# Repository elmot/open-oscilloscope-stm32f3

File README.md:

## Open-Source Oscilloscope based on NUCLEO-F303RE

Some ideas got from Tomasz Ostrowski's [Miniscope](http://tomeko.net/miniscope_v4/index.php?lang=en).
Tomasz has a bunch of ready-to-use-devices, and I have the only preliminary schematics and raw prototype.

The main idea is to build PC-oscilloscope. Hardware is ST Microelectronics development board
[NUCLEO-F303RE](http://www.st.com/en/evaluation-tools/nucleo-f303re.html) plus small additional board with simple protection circuits and basic voltage dividers.

A special Java application or web browser is supposed to be a PC part of the system.

## DISCLAIMER

**! WARNING !**

Read [SAFETY DISCLAIMER](DISCLAIMER.md) before using any of materials listed here.  

### License:
[MIT](license.txt)

### Hardware variants
* Naked Nucleo
  * _No overvoltage protection_
  * Input voltage: 0..3V uni-polar
* Shield board + Nucleo
  * Overvoltage protection
  * Input voltage: 0..30V uni-polar
  * Max. input impedance ~200kOhm

### Usage HOWTO
TBD

### Build HOWTO

#### Required tools
* cmake 3.9.x
* arm-none-eabi-gcc 5.4 + binutils

#### Build firmware
* `mkdir target`
* `cd target`
* `cmake -DCMAKE_TOOLCHAIN_FILE=STM32F303RETx_FLASH.cmake ..`
* `make`

#### Flash firmware
* Connect NUCLEO board
* Copy generated file (_cmake-build-debug/f3_nucleo_oscilloscope.bin_) to NUCLEO virtual drive
* Unmount NUCLEO virtual drive
 
### Roadmap
See [ROADMAP.md](ROADMAP.md)

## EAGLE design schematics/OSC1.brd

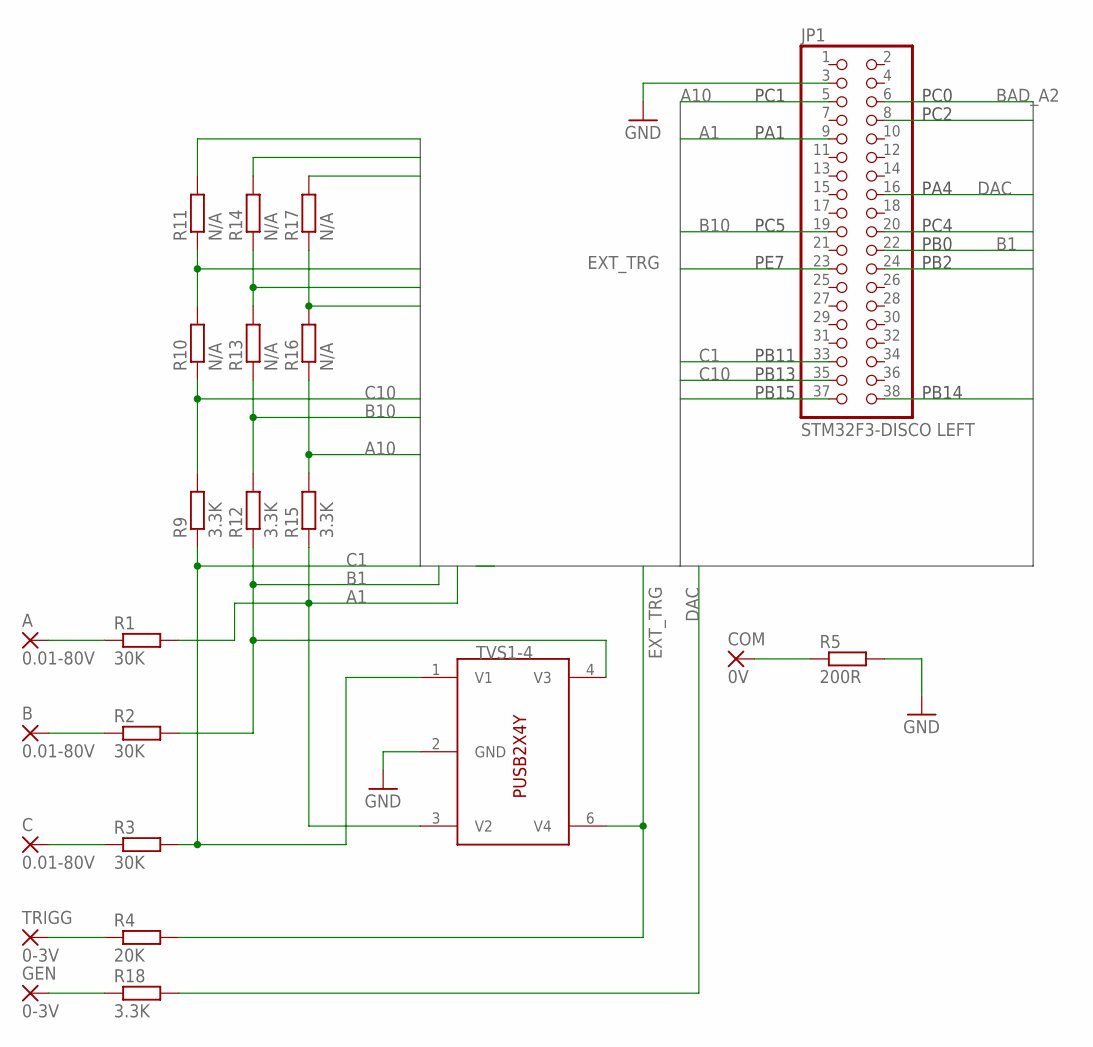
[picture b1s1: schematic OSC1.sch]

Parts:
A: 0.01-80V; 2,54/0,8
B: 0.01-80V; 2,54/0,8
C: 0.01-80V; 2,54/0,8
COM: 0V; 2,54/0,8
GEN: 0-3V; 2,54/0,8
JP1: STM32F3-DISCO LEFT; 2X19
R1, R2, R3: 30K; R1206
R4: 20K; R1206
R5: 200R; R1206
R9, R12, R15, R18: 3.3K; R1206
R10, R11, R13, R14, R16, R17: N/A; R1206
TRIGG: 0-3V; 2,54/0,8
TVS1-4: PUSB2X4Y; SOT363_PHILIPS

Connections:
A1: JP1.9, R1.2, R15.1, TVS1-4.3 (V2)
A10: JP1.5, R15.2, R16.1
B1: JP1.22, R2.2, R12.1, TVS1-4.4 (V3)
B10: JP1.19, R12.2, R13.1
BAD_A2: JP1.6, R17.2
BAD_A10: JP1.8, R16.2, R17.1
BAD_B2: JP1.24, R14.2
BAD_B10: JP1.20, R13.2, R14.1
BAD_C2: JP1.38, R11.2
BAD_C10: JP1.37, R10.2, R11.1
C1: JP1.33, R3.2, R9.1, TVS1-4.1 (V1)
C10: JP1.35, R9.2, R10.1
DAC: JP1.16, R18.2
EXT_TRG: JP1.23, R4.2, TVS1-4.6 (V4)
GND: JP1.3, R5.2, TVS1-4.2 (GND)
unnamed: COM.1, R5.1
unnamed: A.1, R1.1
unnamed: R4.1, TRIGG.1
unnamed: C.1, R3.1
unnamed: B.1, R2.1
unnamed: GEN.1, R18.1

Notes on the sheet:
PA1
PB11
PB0
PA4
PC1
PC0
PC2
PB2
PC4
PC5
PB13
PB14
PB15
PE7

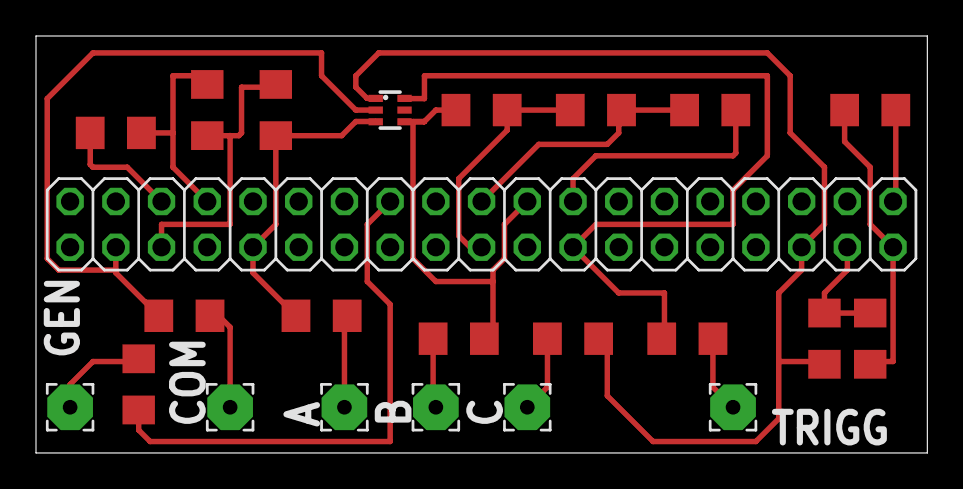
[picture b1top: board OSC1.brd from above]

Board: 2 copper layers, 49.5 x 23.2 mm, 23 parts (0 on the bottom side), 21 nets.

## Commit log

2015-11-21 USB exchange
2016-01-18 Chrome client 1st prototype, USB data exchange works
2016-01-18 removed useless stuff
2016-01-18 PCB picture added
2016-01-19 Gain control; Fixed timing; triangle generation; UI improvements
2016-01-19 Published to Chrome Store
2016-01-21 New icon
2016-01-21 Unnecessary files removed
2016-01-21 Better parameters handling.
2016-01-21 Timing, Range instead of gain, better design
2016-01-21 Ignore. iex
2016-01-21 Pin names corrected
2016-01-21 Latest binary
2016-01-21 Latest screenshots
2016-01-21 Version updated
2016-01-22 Readme updated
2016-01-22 A2 &A 10 fixed
2016-01-23 3 channels, different timing up to 5MHz
2016-01-23 No Jannson
2016-01-23 Pins fixes
2016-01-23 Three channels
2016-01-23 Refactoring+three channels support
2016-01-23 Range fixed
2016-01-23 3 channels; CubeMX bug workaround
2016-01-23 3 channels
2016-01-23 3 Channels work for the very first time.
2016-01-23 Shitty code fix
2016-01-23 UI improvements, refactoring
2016-01-23 Trigger Channel A support, refactoring
2016-01-24 Fast mode dropped from roadmap + small changes
2016-01-24 UI improvements
2016-01-24 Refactoring
2016-01-24 3 channel triggers
2016-01-24 Drop non-key frame if key frame is received
2016-01-24 Triggers better support, refactoring
2016-01-24 No DMA mem-to-mem
2016-01-24 Curve shapes improved
2016-01-24 Market update v.0.0.3
2016-01-25 Non-key frame buffering, better trigger stability
2016-01-25 select_tests
2016-01-25 Play around options
2017-02-05 Restart almost from scratch, new CubeMX, USB CDC instead of USB Vendor-Specific
2017-02-05 DMA_IRQ_SETTINGS
2017-02-05 Semihosting lib
2017-02-05 DMA interrupts and basic data copy
2017-02-06 USB Support started.
2017-02-07 Send data step 1
2017-02-08 JavaFX client
2017-03-05 Single-channel, no triggers
2017-03-07 JavaFX + RXTX library
2017-03-07 next step towards to triggers
2017-03-09 Unfinished web gateway
2017-03-09 Semihosting detection
2017-03-10 Http version phase I
2017-03-10 Http version phase II
2017-03-11 Web part ms 1 works, ready to implement HW commands
2017-03-13 Step 2 towards to triggers
2017-03-13 ADC high rate problem detected but not fixed
2017-03-14 ADC high rate fixed
2017-03-14 Frame queue reset when command is sent to the device
2017-03-14 Cube rerun
2017-03-14 JS optimization
2017-03-14 Some improvements
2017-03-15 Fix typo
2017-03-15 Trigger works 1/2
2017-03-15 Next step towards to trigger
2017-03-16 Switch ACM protocol version to 0
2017-03-16 UART recv binary error detection
2017-03-16 Triggers work. Pre-trigger has glitches
2017-03-16 Some fixes
2017-03-16 Unified command parse
2017-03-17 Gen step 1
2017-03-17 Java FX is not supported
2017-03-17 No AT protocol in USB CDC descriptor
2017-03-17 Generator works
2017-03-17 STM Virtual Port driver for Windows is added
2017-03-17 icons+html improvements
2017-03-17 Front update (#2)
    Front update, html improvements
2017-03-17 Restore app icon
2017-03-17 Sine wave; Less generator overhead
2017-03-17 Skip garbage from UART?
2017-03-17 Resolve race conditions?
2017-03-17 Restore dividers for chanel B
2017-03-17 Error message more visible
2017-03-17 Store and init confids, part 1
2017-03-17 Comm. protocol v1.1
2017-03-18 icon fix
2017-03-18 Comm. protocol v2.0
2017-03-19 Don't ignore .exe
2017-03-19 No gzip, better error handling
2017-03-19 NPE protection
2017-03-19 Buggy frame bursting
2017-03-19 Frame bursting fix
2017-03-19 Refactiring and fixes
2017-03-19 Some fixes; diagnostics; config sync; reasonable defaults
2017-03-19 Get rid of CommThread
2017-03-19 JavaFX version works again
2017-03-19 Com port choice in JavaFX app
2017-03-20 JavaFX optimised and fixed
2017-03-20 Various timing fixes
2017-03-21 CMake issue fixed
2017-03-21 .hex and .bin files generation
2017-03-21 Universal CLI launcher
2017-03-21 No extra Thread.yield
2017-03-21 Better screen update timing
2017-03-21 Build .dfu, fix 'make clean'
2017-03-21 Documentation
2017-03-21 Release script
2017-03-21 Fix links
2017-03-21 Fix Disclaimer
2017-03-21 Temporary disable channels B and C
2017-03-22 More stable communications, setting port
2017-03-22 Optimize FPS counter
2017-03-22 Numerous fixes and improvements
2017-03-22 Small improvements
2017-03-23 Release assembly process with mvn
2017-03-23 Parameters setting improvements
2017-03-23 Ship both web and javafx versions
2017-03-23 Voltage/time outpur
2017-03-24 PCB files merged from another branch
2017-03-24 - Electrical parameters change - schematics + readme
2017-03-24 - Electrical parameters change - FirmWare
2017-03-24 Firmware initial settings fixed
2017-03-24 - Electrical parameters change - Client
2017-03-24 Change buffering default
2017-04-04 Timing and voltage units displayed
2017-04-04 Fix trigger picking off
2017-04-09 Measurements + some refactoring
2017-04-16 SVD->C generator first draft
2017-04-16 OpenOCD/extrenal GDB support
2017-04-16 SVD generator support 1st try
2017-04-16 Small fix
2017-04-17 Upgrade to next cube
2017-04-17 New peripheral generator
2017-04-17 No packed attribute
2017-04-17 Alternative registers to unions.
2017-05-02 Roughly fix line feeds
2017-05-02 Make like utility
2017-06-10 Basic triangle generator
2017-06-10 TFMs
2017-06-11 Electron client
2017-06-11 Run configurations
2017-06-11 Simple data transfer
2017-06-14 Basic electron client
2017-06-26 NW.js client instead of electron
2017-06-26 Add hardware definitions
2017-06-26 nw client runner
2017-06-27 Basic triggers, no copy frame yet
2017-07-03 Send keyframes, optimize communication
2017-07-05 UART at 2 Mbit
2021-09-16 Bump commons-io from 2.5 to 2.7 in /client
    Bumps commons-io from 2.5 to 2.7.
    ---
    updated-dependencies:
    - dependency-name: commons-io:commons-io
    dependency-type: direct:production
    ...
2021-09-27 Bump commons-io from 2.5 to 2.7 in /client (#3)
    Bumps commons-io from 2.5 to 2.7.
    ---
    updated-dependencies:
    - dependency-name: commons-io:commons-io
    dependency-type: direct:production
    ...
